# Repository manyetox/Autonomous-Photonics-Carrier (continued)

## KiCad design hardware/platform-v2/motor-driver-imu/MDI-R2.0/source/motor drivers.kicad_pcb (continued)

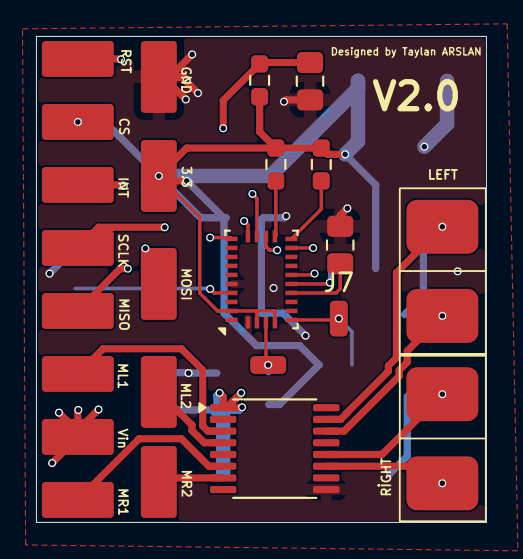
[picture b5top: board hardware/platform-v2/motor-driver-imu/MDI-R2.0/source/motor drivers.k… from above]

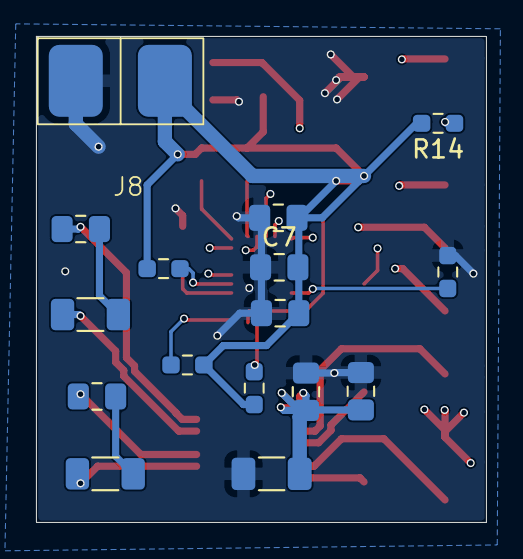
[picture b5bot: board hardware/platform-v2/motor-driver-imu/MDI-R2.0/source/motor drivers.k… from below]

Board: 4 copper layers, 25.0 x 27.0 mm, 28 parts (16 on the bottom side), 26 nets.

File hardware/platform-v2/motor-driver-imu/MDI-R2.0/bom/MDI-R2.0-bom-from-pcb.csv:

Quantity,References,Value / Part,Footprint,Source
1,C21,0.1u,Capacitor_SMD:C_0805_2012Metric_Pad1.18x1.45mm_HandSolder,Auto-extracted from KiCad PCB; verify against schematic before ordering
4,"C4, C7, C8, C9",0.1uF,Capacitor_SMD:C_0805_2012Metric_Pad1.18x1.45mm_HandSolder,Auto-extracted from KiCad PCB; verify against schematic before ordering
2,"C27, C28",100n,Capacitor_SMD:C_0805_2012Metric_Pad1.18x1.45mm_HandSolder,Auto-extracted from KiCad PCB; verify against schematic before ordering
1,C26,100u,Capacitor_SMD:C_1206_3216Metric_Pad1.33x1.80mm_HandSolder,Auto-extracted from KiCad PCB; verify against schematic before ordering
6,"R12, R13, R14, R18, R3, R4",10k,Resistor_SMD:R_0603_1608Metric_Pad0.98x0.95mm_HandSolder,Auto-extracted from KiCad PCB; verify against schematic before ordering
1,C25,10u,Capacitor_SMD:C_0805_2012Metric_Pad1.18x1.45mm_HandSolder,Auto-extracted from KiCad PCB; verify against schematic before ordering
2,"R15, R16",4.7k,Resistor_SMD:R_0603_1608Metric_Pad0.98x0.95mm_HandSolder,Auto-extracted from KiCad PCB; verify against schematic before ordering
1,C2,4.7uF,Capacitor_SMD:C_0805_2012Metric_Pad1.18x1.45mm_HandSolder,Auto-extracted from KiCad PCB; verify against schematic before ordering
2,"R23, R24",47,Resistor_SMD:R_1206_3216Metric_Pad1.30x1.75mm_HandSolder,Auto-extracted from KiCad PCB; verify against schematic before ordering
1,BMO1,BNO086,Package_LGA:LGA-28_5.2x3.8mm_P0.5mm,Auto-extracted from KiCad PCB; verify against schematic before ordering
2,"J6, J7",BNO_BOOT_Test_pin,Connector_Wire:SolderWirePad_1x01_SMD_1x2mm,Auto-extracted from KiCad PCB; verify against schematic before ordering
1,J1,Conn_01x13_Pin,Library-kicad:13-conn-smd-dual,Auto-extracted from KiCad PCB; verify against schematic before ordering
3,"J4, J5, J8",Screw_Terminal_01x02,Library-kicad:power pad dual,Auto-extracted from KiCad PCB; verify against schematic before ordering
1,TC78H651FNG1,"TC78H651FGN,EL",Package_SO:TSSOP-16_4.4x5mm_P0.65mm,Auto-extracted from KiCad PCB; verify against schematic before ordering

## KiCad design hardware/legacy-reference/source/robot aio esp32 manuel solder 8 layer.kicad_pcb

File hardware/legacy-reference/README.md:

# Legacy robot-controller reference — not a photonics platform version

This folder contains a pre-project ESP32 robot-controller design that influenced later embedded/motor-control work.

It is included only for design history and reusable engineering reference. It is **not** “Platform V0,” “Platform V1,” or a current photonics-carrier PCB.

Do not use its filename/versioning vocabulary when citing the autonomous-photonics carrier.

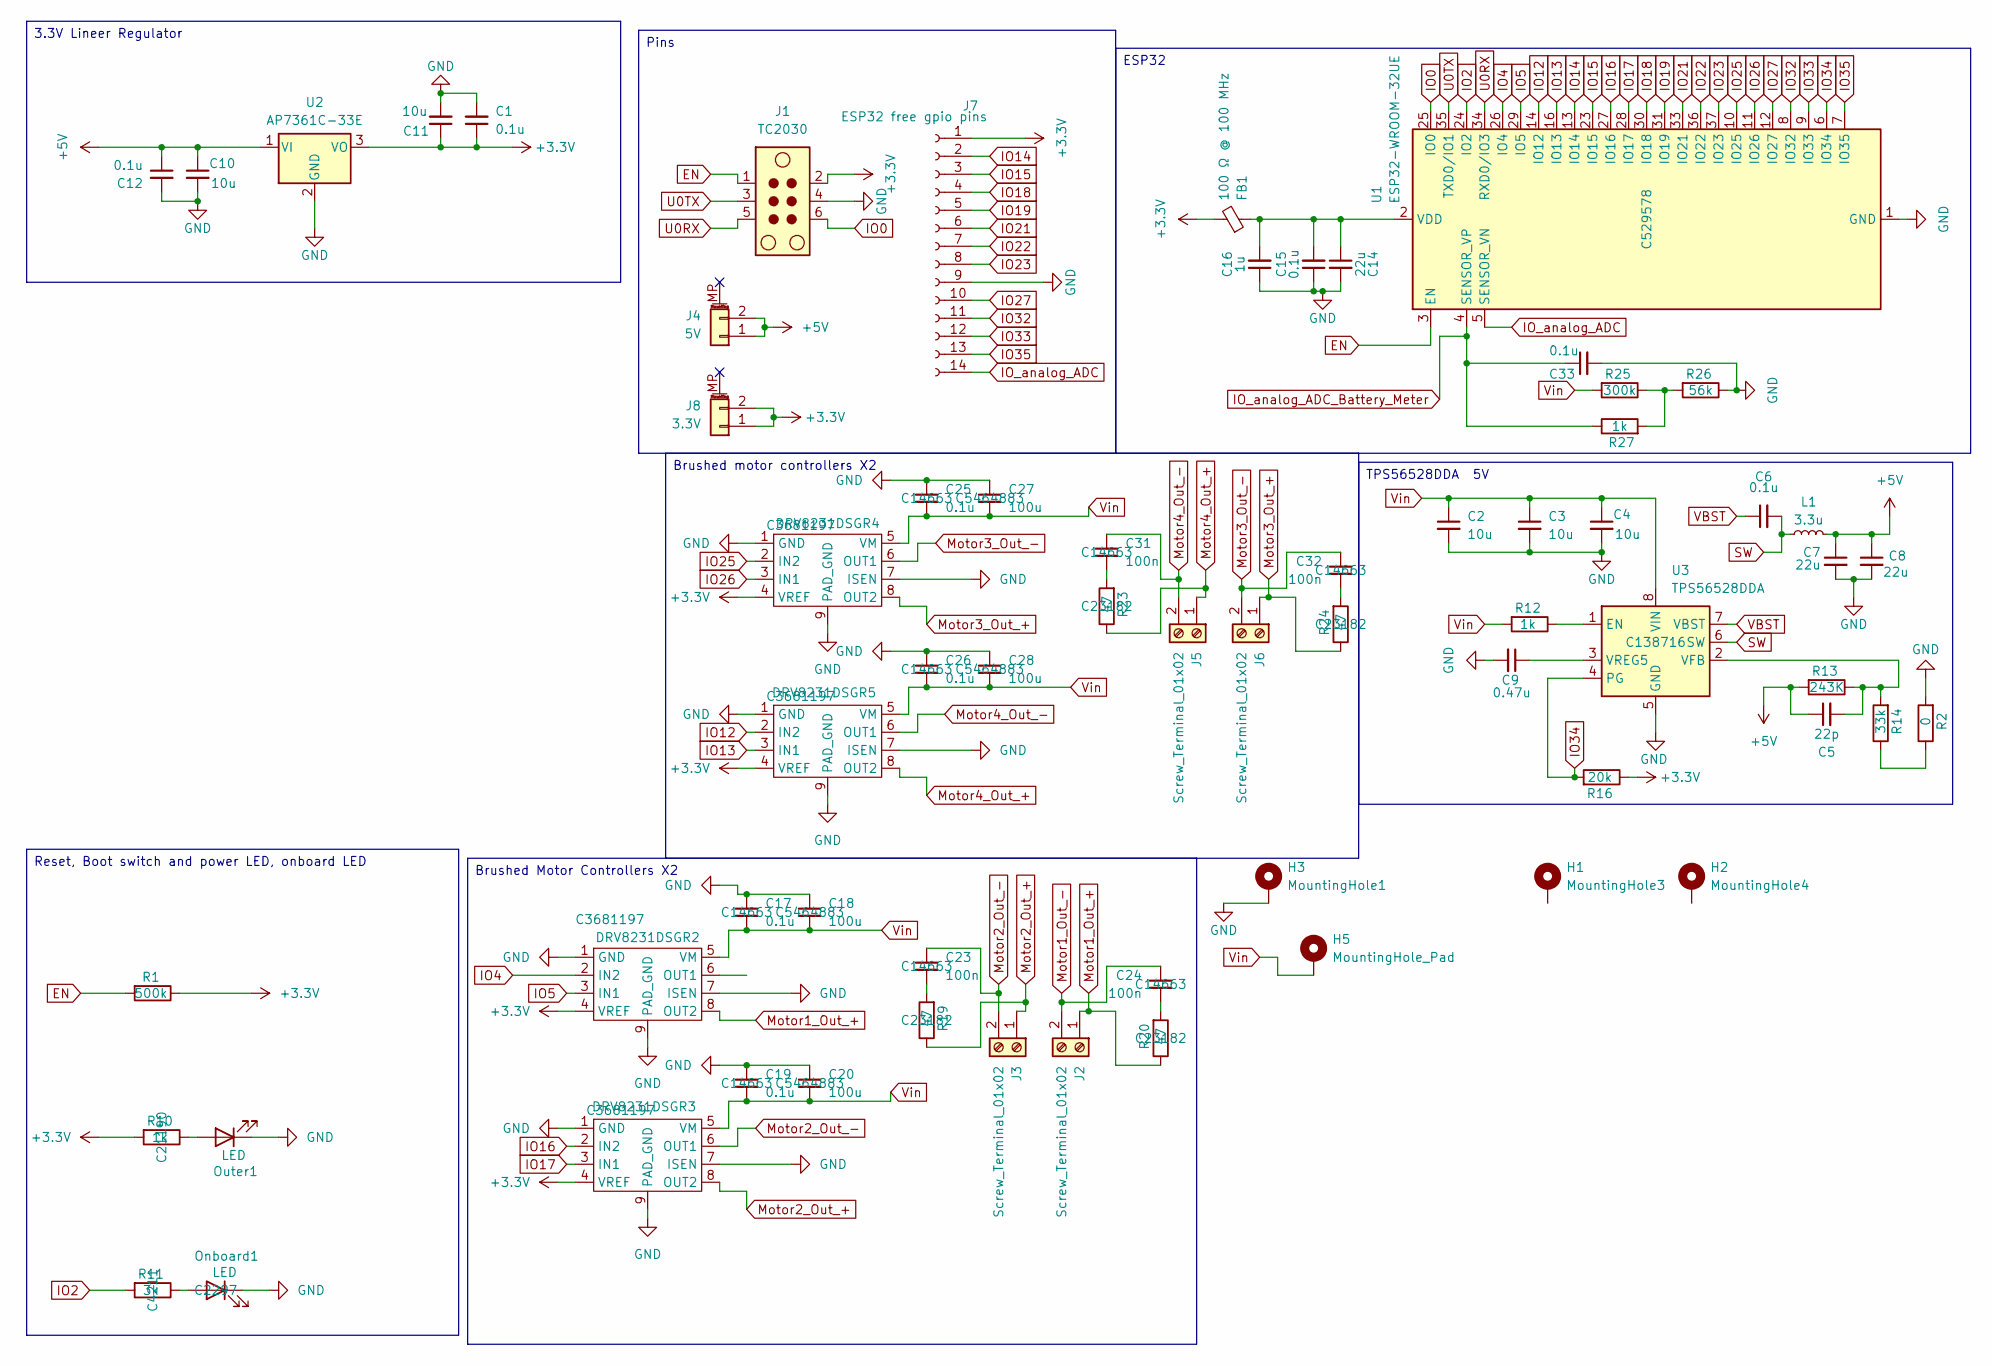
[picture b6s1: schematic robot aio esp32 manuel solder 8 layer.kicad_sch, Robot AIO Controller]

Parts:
C1, C12: 0.1u; C_1206_3216Metric; LCSC Part # C15850
C2, C3, C4, C10, C11: 10u; C_1206_3216Metric; LCSC Part # C15850
C5: 22p; C_1206_3216Metric; LCSC Part # C1653
C6, C15, C17, C19, C25, C26, C33: 0.1u; C_1206_3216Metric; LCSC Part # C14663
C7, C8, C14: 22u; C_1206_3216Metric; LCSC Part # C45783
C9: 0.47u; C_1206_3216Metric; LCSC Part # C1623
C16: 1u; C_1206_3216Metric; LCSC Part # C15849
C18, C20, C27, C28: 100u; C_Radial_D6.3mm_H5.0mm_P2.50mm; LCSC Part # C5464883
C23, C24, C31, C32: 100n; C_1206_3216Metric; LCSC Part # C14663
DRV8231DSGR2, DRV8231DSGR3, DRV8231DSGR4, DRV8231DSGR5: HSOP-8-1EP_3.9x4.9mm_P1.27mm_EP2.41x3.1mm_ThermalVias; LCSC Part # C3681197
FB1: 100 Ω @ 100 MHz; L_1206_3216Metric; LCSC Part # C1015
H1: MountingHole3; MountingHole_2.2mm_M2_DIN965_Pad_TopBottom
H2: MountingHole4; MountingHole_2.2mm_M2_DIN965_Pad_TopBottom
H3: MountingHole1; MountingHole_2.2mm_M2_DIN965_Pad_TopBottom
H5: MountingHole_Pad; MountingHole_2.2mm_M2_DIN965_Pad_TopBottom
J1: TC2030; PinHeader_2x03_P1.27mm_Vertical
J2, J3, J5, J6: Screw_Terminal_01x02; TerminalBlock_4Ucon_1x02_P3.50mm_Horizontal
J4: 5V; PinHeader_1x02_P1.27mm_Vertical
J7: ESP32 free gpio pins; PinHeader_1x14_P2.00mm_Vertical
J8: 3.3V; PinHeader_1x02_P1.27mm_Vertical
L1: 3.3u; L_10.4x10.4_H4.8
Onboard1: LED; LED_D3.0mm; LCSC Part # C2297
Outer1: LED; LED_D3.0mm
R1: 500k; R_0805_2012Metric_Pad1.20x1.40mm_HandSolder; LCSC Part # C21190
R2: 0; R_1206_3216Metric; LCSC Part # C4216
R10, R12, R27: 1k; R_1206_3216Metric; LCSC Part # C21190
R11: 3k; R_1206_3216Metric; LCSC Part # C4211
R13: 243K; R_1206_3216Metric; LCSC Part # C22807
R14: 33k; R_1206_3216Metric; LCSC Part # C4216
R16: 20k; R_1206_3216Metric; LCSC Part # C4184
R19, R20, R23, R24: 47; R_1206_3216Metric; LCSC Part # C23182
R25: 300k; R_1206_3216Metric; LCSC Part # C23024
R26: 56k; R_1206_3216Metric; LCSC Part # C23206
U1: ESP32-WROOM-32UE; LCSC Part # C529578
U2: AP7361C-33E; SOT-223-3_TabPin2
U3: TPS56528DDA; Texas_HSOP-8-1EP_3.9x4.9mm_P1.27mm_ThermalVias; LCSC Part # C138716

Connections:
+3.3V: C1.1, C11.1, DRV8231DSGR2.4 (VREF), DRV8231DSGR3.4 (VREF), DRV8231DSGR4.4 (VREF), DRV8231DSGR5.4 (VREF), FB1.2, J1.2, J7.1, J8.1, J8.2, R1.1, R10.2, R16.1, U2.3 (VO)
+5V: C5.1, C7.1, C8.1, C10.1, C12.1, J4.1, J4.2, L1.2, R13.2, U2.1 (VI)
EN: J1.1, R1.2, U1.3 (EN)
GND: C1.2, C2.2, C3.2, C4.2, C7.2, C8.2, C9.2, C10.2, C11.2, C12.2, C14.2, C15.1, C16.1, C17.1, C18.1, C19.1, C20.1, C25.1, C26.1, C27.1, C28.1, C33.2, DRV8231DSGR2.1 (GND), DRV8231DSGR2.7 (ISEN), DRV8231DSGR2.9 (PAD_GND), DRV8231DSGR3.1 (GND), DRV8231DSGR3.7 (ISEN), DRV8231DSGR3.9 (PAD_GND), DRV8231DSGR4.1 (GND), DRV8231DSGR4.7 (ISEN), DRV8231DSGR4.9 (PAD_GND), DRV8231DSGR5.1 (GND), DRV8231DSGR5.7 (ISEN), DRV8231DSGR5.9 (PAD_GND), H3.MP, J1.4, J7.9, Onboard1.1 (K), Outer1.1 (K), R2.2, R26.1, U1.1 (GND), U1.15 (GND), U1.38 (GND), U1.39 (GND), U2.2 (GND), U3.5 (GND), U3.9 (GND)
IO0: J1.6, U1.25 (IO0)
IO2: R11.2, U1.24 (IO2)
IO4: DRV8231DSGR2.2 (IN2), U1.26 (IO4)
IO5: DRV8231DSGR2.3 (IN1), U1.29 (IO5)
IO12: DRV8231DSGR5.2 (IN2), U1.14 (IO12)
IO13: DRV8231DSGR5.3 (IN1), U1.16 (IO13)
IO14: J7.2, U1.13 (IO14)
IO15: J7.3, U1.23 (IO15)
IO16: DRV8231DSGR3.2 (IN2), U1.27 (IO16)
IO17: DRV8231DSGR3.3 (IN1), U1.28 (IO17)
IO18: J7.4, U1.30 (IO18)
IO19: J7.5, U1.31 (IO19)
IO21: J7.6, U1.33 (IO21)
IO22: J7.7, U1.36 (IO22)
IO23: J7.8, U1.37 (IO23)
IO25: DRV8231DSGR4.2 (IN2), U1.10 (IO25)
IO26: DRV8231DSGR4.3 (IN1), U1.11 (IO26)
IO27: J7.10, U1.12 (IO27)
IO32: J7.11, U1.8 (IO32)
IO33: J7.12, U1.9 (IO33)
IO34: R16.2, U1.6 (IO34), U3.4 (PG)
IO35: J7.13, U1.7 (IO35)
IO_analog_ADC: J7.14, U1.5 (SENSOR_VN)
IO_analog_ADC_Battery_Meter: C33.1, R27.1, U1.4 (SENSOR_VP)
Motor1_Out_+: DRV8231DSGR2.8 (OUT2), J2.1, R20.1
Motor1_Out_-: C24.1, J2.2
Motor2_Out_+: DRV8231DSGR3.8 (OUT2), J3.1, R19.1
Motor2_Out_-: C23.1, DRV8231DSGR3.6 (OUT1), J3.2
Motor3_Out_+: DRV8231DSGR4.8 (OUT2), J6.1, R24.1
Motor3_Out_-: C32.1, DRV8231DSGR4.6 (OUT1), J6.2
Motor4_Out_+: DRV8231DSGR5.8 (OUT2), J5.1, R23.1
Motor4_Out_-: C31.1, DRV8231DSGR5.6 (OUT1), J5.2
unnamed: C23.2, R19.2
unnamed: C24.2, R20.2
unnamed: C31.2, R23.2
unnamed: C32.2, R24.2
unnamed: Onboard1.2 (A), R11.1
unnamed: Outer1.2 (A), R10.1
unnamed: R2.1, R14.1
unnamed: R25.1, R26.2, R27.2
unnamed: C14.1, C15.2, C16.2, FB1.1, U1.2 (VDD)
unnamed: R12.1, U3.1 (EN)
unnamed: C5.2, R13.1, R14.2, U3.2 (VFB)
unnamed: C9.1, U3.3 (VREG5)
SW: C6.2, L1.1, U3.6 (SW)
U0RX: J1.5, U1.34 (RXD0/IO3)
U0TX: J1.3, U1.35 (TXD0/IO1)
VBST: C6.1, U3.7 (VBST)
Vin: C2.1, C3.1, C4.1, C17.2, C18.2, C19.2, C20.2, C25.2, C26.2, C27.2, C28.2, DRV8231DSGR2.5 (VM), DRV8231DSGR3.5 (VM), DRV8231DSGR4.5 (VM), DRV8231DSGR5.5 (VM), H5.1, R12.2, R25.2, U3.8 (VIN)

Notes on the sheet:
ESP32
Brushed Motor Controllers X2
Brushed motor controllers X2
Reset, Boot switch and power LED, onboard LED
TPS56528DDA 5V
3.3V Lineer Regulator
Pins

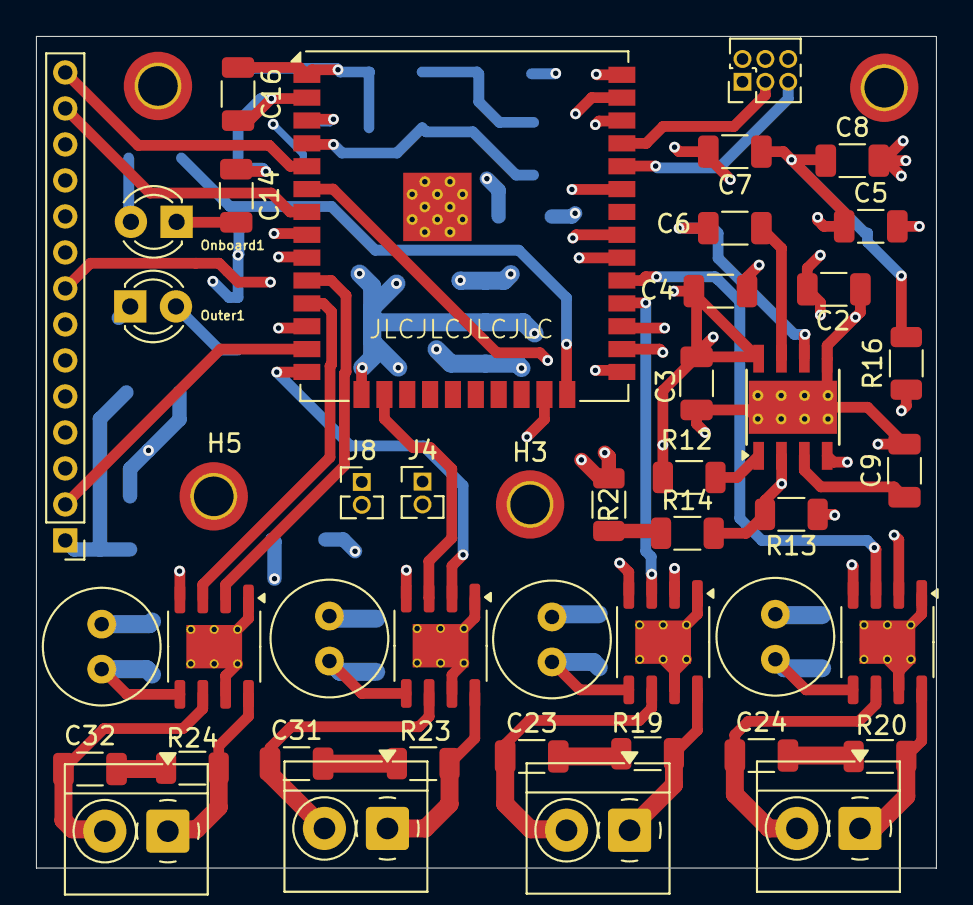
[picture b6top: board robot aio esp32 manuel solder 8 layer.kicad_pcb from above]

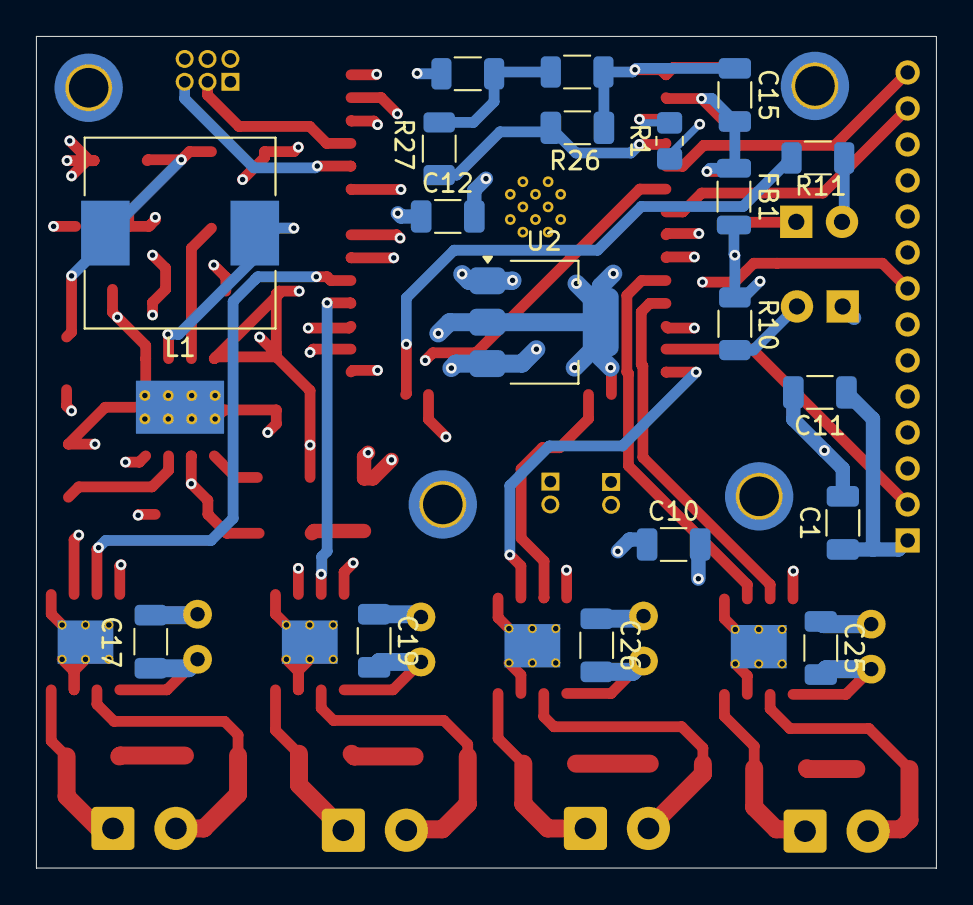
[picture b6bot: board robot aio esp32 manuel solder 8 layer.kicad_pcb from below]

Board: 8 copper layers, 50.0 x 46.2 mm, 66 parts (19 on the bottom side), 53 nets.

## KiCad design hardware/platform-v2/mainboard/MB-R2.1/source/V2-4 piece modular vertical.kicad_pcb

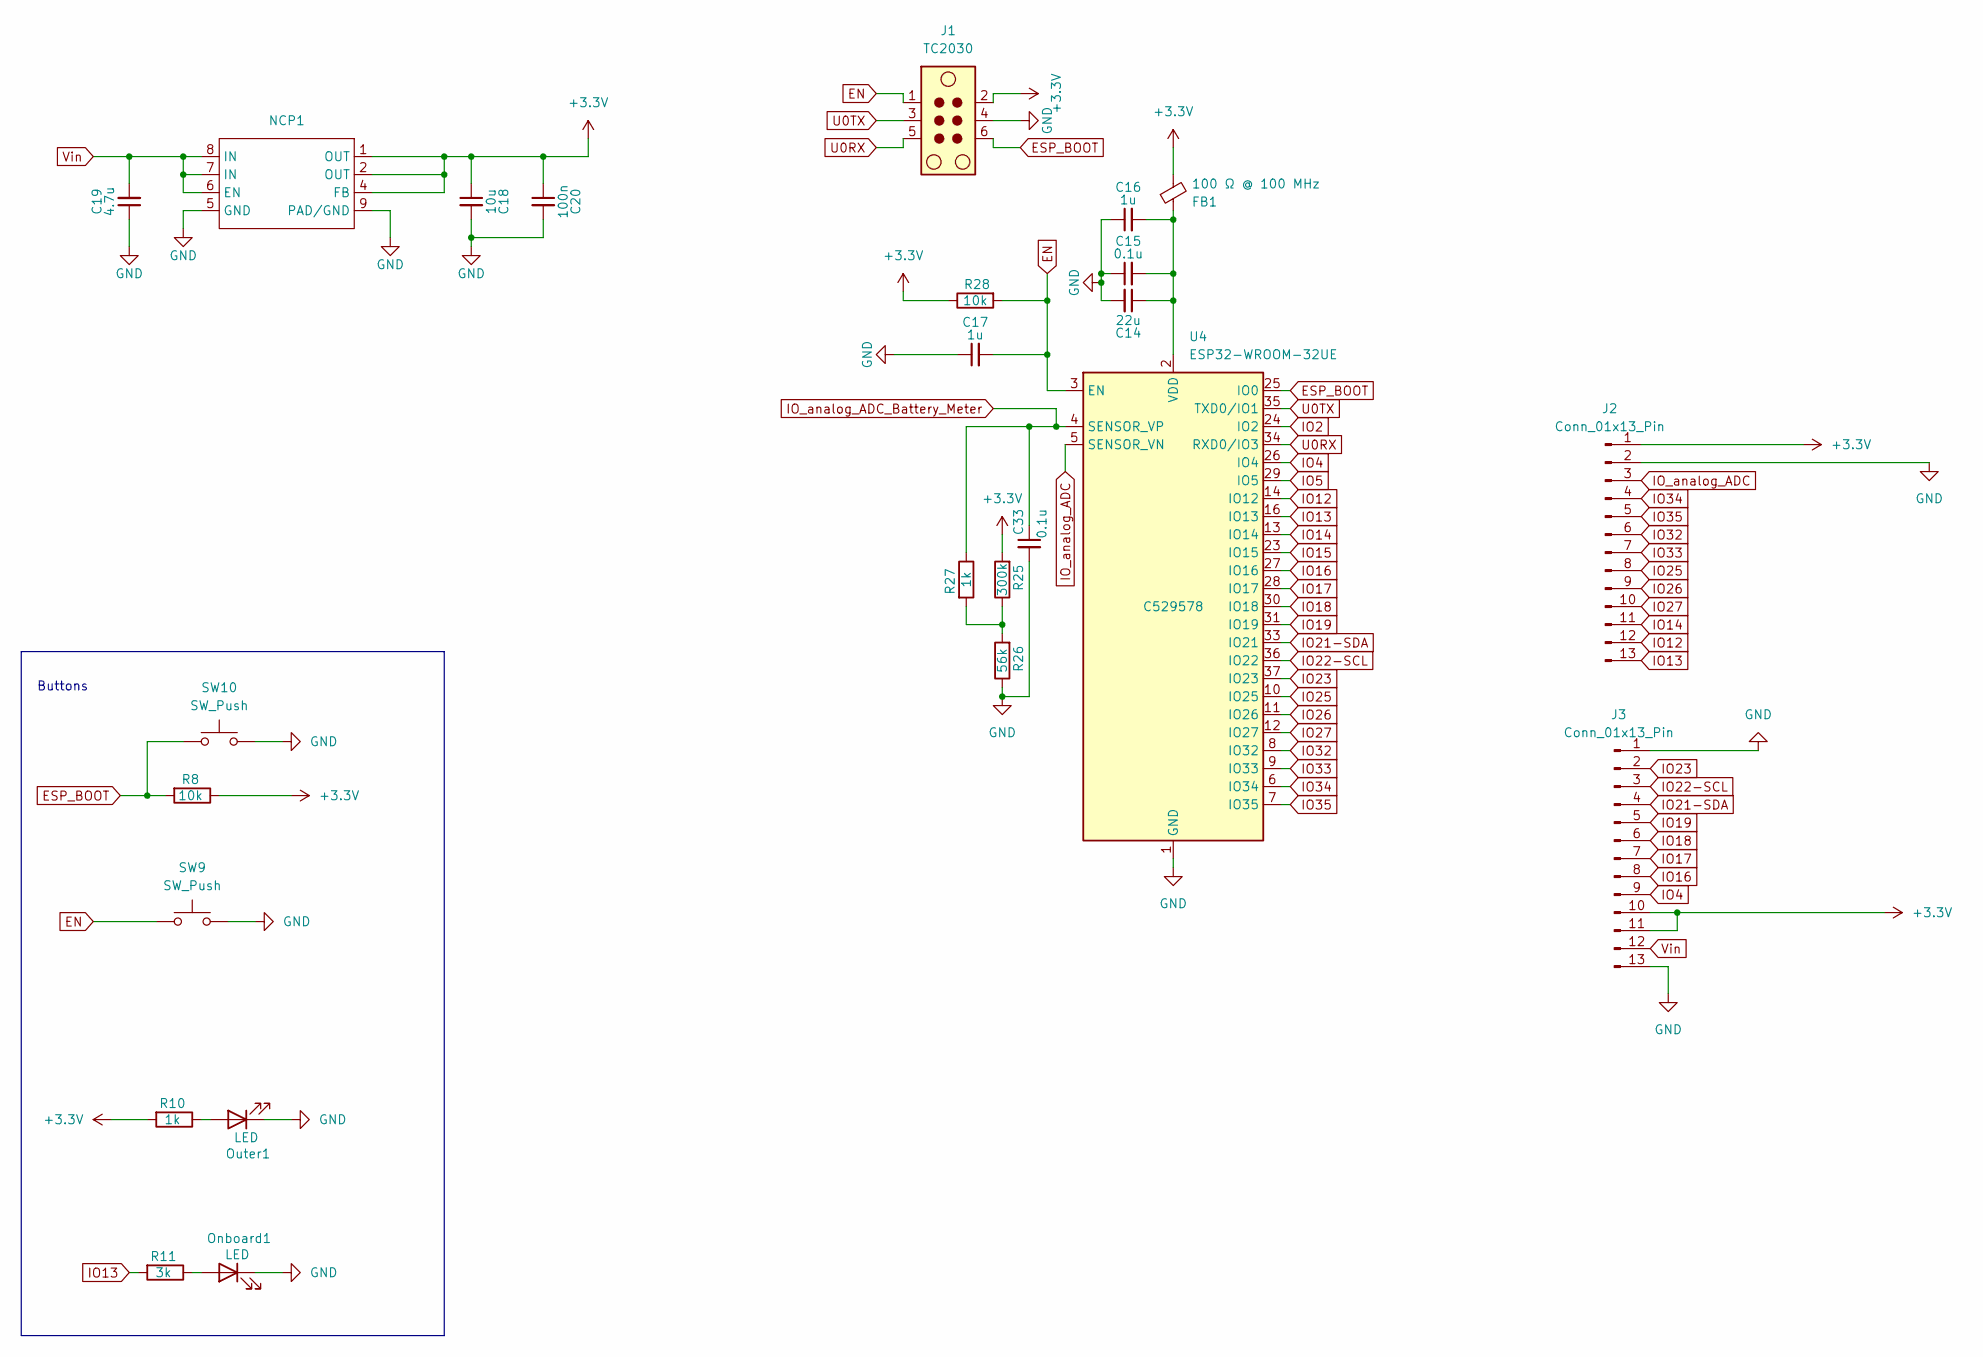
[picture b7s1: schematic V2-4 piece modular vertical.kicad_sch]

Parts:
C14: 22u; C_0805_2012Metric_Pad1.18x1.45mm_HandSolder; LCSC Part # C45783
C15, C33: 0.1u; C_0805_2012Metric_Pad1.18x1.45mm_HandSolder; LCSC Part # C14663
C16, C17: 1u; C_0805_2012Metric_Pad1.18x1.45mm_HandSolder; LCSC Part # C15849
C18: 10u; C_0805_2012Metric_Pad1.18x1.45mm_HandSolder; LCSC Part # C15849
C19: 4.7u; C_0805_2012Metric_Pad1.18x1.45mm_HandSolder; LCSC Part # C15849
C20: 100n; C_0805_2012Metric_Pad1.18x1.45mm_HandSolder; LCSC Part # C15849
FB1: 100 Ω @ 100 MHz; L_1206_3216Metric; LCSC Part # C1015
J1: TC2030; PinHeader_2x03_P1.27mm_Vertical
J2, J3: Conn_01x13_Pin; 13-conn-smd-dual
NCP1: XDFN-8, 1.6 × 1.2 mm, 0.4 mm pitch
Onboard1: LED; LED_0805_2012Metric_Pad1.15x1.40mm_HandSolder; LCSC Part # C2297
Outer1: LED; LED_0805_2012Metric_Pad1.15x1.40mm_HandSolder
R8, R28: 10k; R_0805_2012Metric_Pad1.20x1.40mm_HandSolder; LCSC Part # C21190
R10, R27: 1k; R_0805_2012Metric_Pad1.20x1.40mm_HandSolder; LCSC Part # C21190
R11: 3k; R_0805_2012Metric_Pad1.20x1.40mm_HandSolder; LCSC Part # C4211
R25: 300k; R_0805_2012Metric_Pad1.20x1.40mm_HandSolder; LCSC Part # C23024
R26: 56k; R_0805_2012Metric_Pad1.20x1.40mm_HandSolder; LCSC Part # C23206
SW9, SW10: SW_Push; SW_SPST_CK_KXT3
U4: ESP32-WROOM-32UE; LCSC Part # C529578

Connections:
+3.3V: C18.1, C20.1, FB1.2, J1.2, J2.1, J3.10, J3.11, NCP1.1 (OUT), NCP1.2 (OUT), NCP1.4 (FB), R8.1, R10.2, R25.2, R28.1
EN: C17.2, J1.1, R28.2, SW9.1, U4.3 (EN)
ESP_BOOT: J1.6, R8.2, SW10.1, U4.25 (IO0)
GND: C14.2, C15.1, C16.1, C17.1, C18.2, C19.1, C20.2, C33.2, J1.4, J2.2, J3.1, J3.13, NCP1.5 (GND), NCP1.9 (PAD/GND), Onboard1.1 (K), Outer1.1 (K), R26.1, SW9.2, SW10.2, U4.1 (GND), U4.15 (GND), U4.38 (GND), U4.39 (GND)
IO2: U4.24 (IO2)
IO4: J3.9, U4.26 (IO4)
IO5: U4.29 (IO5)
IO12: J2.12, U4.14 (IO12)
IO13: J2.13, R11.2, U4.16 (IO13)
IO14: J2.11, U4.13 (IO14)
IO15: U4.23 (IO15)
IO16: J3.8, U4.27 (IO16)
IO17: J3.7, U4.28 (IO17)
IO18: J3.6, U4.30 (IO18)
IO19: J3.5, U4.31 (IO19)
IO21-SDA: J3.4, U4.33 (IO21)
IO22-SCL: J3.3, U4.36 (IO22)
IO23: J3.2, U4.37 (IO23)
IO25: J2.8, U4.10 (IO25)
IO26: J2.9, U4.11 (IO26)
IO27: J2.10, U4.12 (IO27)
IO32: J2.6, U4.8 (IO32)
IO33: J2.7, U4.9 (IO33)
IO34: J2.4, U4.6 (IO34)
IO35: J2.5, U4.7 (IO35)
IO_analog_ADC: J2.3, U4.5 (SENSOR_VN)
IO_analog_ADC_Battery_Meter: C33.1, R27.1, U4.4 (SENSOR_VP)
unnamed: Onboard1.2 (A), R11.1
unnamed: Outer1.2 (A), R10.1
unnamed: R25.1, R26.2, R27.2
unnamed: C14.1, C15.2, C16.2, FB1.1, U4.2 (VDD)
U0RX: J1.5, U4.34 (RXD0/IO3)
U0TX: J1.3, U4.35 (TXD0/IO1)
Vin: C19.2, J3.12, NCP1.6 (EN), NCP1.7 (IN), NCP1.8 (IN)

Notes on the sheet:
Buttons

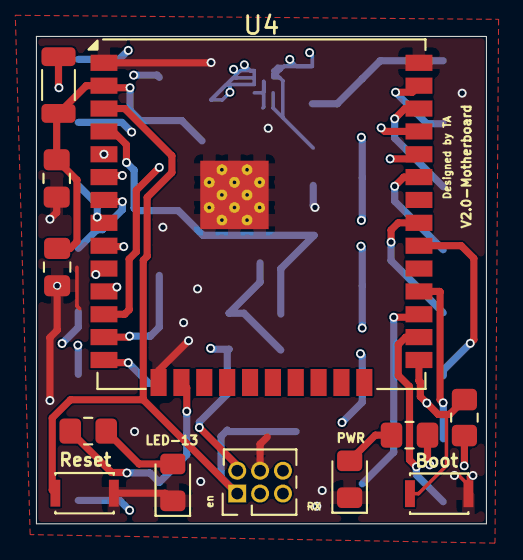
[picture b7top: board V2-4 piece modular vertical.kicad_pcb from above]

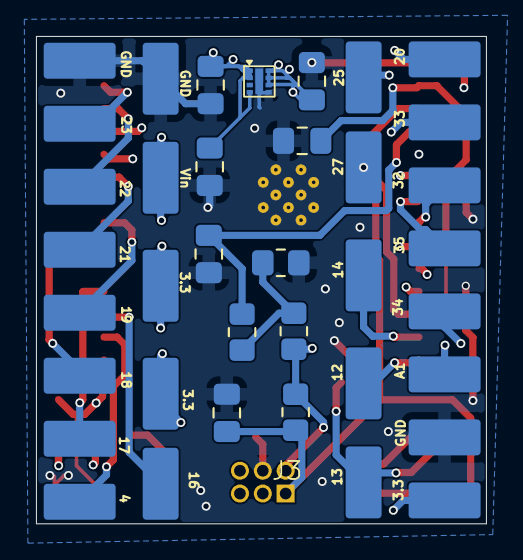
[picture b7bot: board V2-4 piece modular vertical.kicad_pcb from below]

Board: 4 copper layers, 25.0 x 27.1 mm, 25 parts (13 on the bottom side), 31 nets.

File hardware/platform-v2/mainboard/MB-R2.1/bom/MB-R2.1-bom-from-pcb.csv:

Quantity,References,Value / Part,Footprint,Source
2,"C15, C33",0.1u,Capacitor_SMD:C_0805_2012Metric_Pad1.18x1.45mm_HandSolder,Auto-extracted from KiCad PCB; verify against schematic before ordering
1,FB1,100 Ω @ 100 MHz,Inductor_SMD:L_1206_3216Metric,Auto-extracted from KiCad PCB; verify against schematic before ordering
1,C20,100n,Capacitor_SMD:C_0805_2012Metric_Pad1.18x1.45mm_HandSolder,Auto-extracted from KiCad PCB; verify against schematic before ordering
2,"R28, R8",10k,Resistor_SMD:R_0805_2012Metric_Pad1.20x1.40mm_HandSolder,Auto-extracted from KiCad PCB; verify against schematic before ordering
1,C18,10u,Capacitor_SMD:C_0805_2012Metric_Pad1.18x1.45mm_HandSolder,Auto-extracted from KiCad PCB; verify against schematic before ordering
2,"R10, R27",1k,Resistor_SMD:R_0805_2012Metric_Pad1.20x1.40mm_HandSolder,Auto-extracted from KiCad PCB; verify against schematic before ordering
2,"C16, C17",1u,Capacitor_SMD:C_0805_2012Metric_Pad1.18x1.45mm_HandSolder,Auto-extracted from KiCad PCB; verify against schematic before ordering
1,C14,22u,Capacitor_SMD:C_0805_2012Metric_Pad1.18x1.45mm_HandSolder,Auto-extracted from KiCad PCB; verify against schematic before ordering
1,R25,300k,Resistor_SMD:R_0805_2012Metric_Pad1.20x1.40mm_HandSolder,Auto-extracted from KiCad PCB; verify against schematic before ordering
1,R11,3k,Resistor_SMD:R_0805_2012Metric_Pad1.20x1.40mm_HandSolder,Auto-extracted from KiCad PCB; verify against schematic before ordering
1,C19,4.7u,Capacitor_SMD:C_0805_2012Metric_Pad1.18x1.45mm_HandSolder,Auto-extracted from KiCad PCB; verify against schematic before ordering
1,R26,56k,Resistor_SMD:R_0805_2012Metric_Pad1.20x1.40mm_HandSolder,Auto-extracted from KiCad PCB; verify against schematic before ordering
2,"J2, J3",Conn_01x13_Pin,Library-kicad:13-conn-smd-dual,Auto-extracted from KiCad PCB; verify against schematic before ordering
1,U4,ESP32-WROOM-32UE,RF_Module:ESP32-WROOM-32UE,Auto-extracted from KiCad PCB; verify against schematic before ordering
2,"Onboard1, Outer1",LED,LED_SMD:LED_0805_2012Metric_Pad1.15x1.40mm_HandSolder,Auto-extracted from KiCad PCB; verify against schematic before ordering
1,NCP1,NCP186AMX330TAG,"Library-kicad:XDFN-8, 1.6 × 1.2 mm, 0.4 mm pitch",Auto-extracted from KiCad PCB; verify against schematic before ordering
2,"SW10, SW9",SW_Push,Button_Switch_SMD:SW_SPST_CK_KXT3,Auto-extracted from KiCad PCB; verify against schematic before ordering
1,J1,TC2030,Connector_PinHeader_1.27mm:PinHeader_2x03_P1.27mm_Vertical,Auto-extracted from KiCad PCB; verify against schematic before ordering

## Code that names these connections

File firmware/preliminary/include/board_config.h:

#pragma once

// Autonomous-Photonics-Carrier — Platform V2 preliminary firmware
// Public scaffold: peripheral mappings remain disabled until the final
// physical daughterboard interconnect is confirmed on the assembled carrier.

namespace apc {

// Confirmed directly from MB-R2.1 PCB routing.
constexpr int PIN_STATUS_LED = 13;

// ESP32-WROOM-32UE pad 4 / SENSOR_VP corresponds to GPIO36 and is labelled
// IO_analog_ADC_Battery_Meter in the current mainboard source. The resistor
// network should be re-checked before interpreting this as true battery voltage.
constexpr int PIN_ADC_DIAGNOSTIC = 36;

// Use -1 to make a signal unavailable. The firmware will not actuate motors
// until every required motor pin has a non-negative mapping.
constexpr int PIN_MOTOR_L_IN1 = -1;
constexpr int PIN_MOTOR_L_IN2 = -1;
constexpr int PIN_MOTOR_R_IN1 = -1;
constexpr int PIN_MOTOR_R_IN2 = -1;

constexpr int PIN_IMU_CS_N   = -1;
constexpr int PIN_IMU_INT_N  = -1;
constexpr int PIN_IMU_RST_N  = -1;
constexpr int PIN_SPI_SCLK   = -1;
constexpr int PIN_SPI_MOSI   = -1;
constexpr int PIN_SPI_MISO   = -1;

constexpr int PIN_PAW_NCS    = -1;
constexpr int PIN_PAW_MOTION = -1;
constexpr int PIN_MA730_CS_L = -1;
constexpr int PIN_MA730_CS_R = -1;

constexpr bool ENABLE_ACTUATION_AT_BOOT = false;

} // namespace apc
